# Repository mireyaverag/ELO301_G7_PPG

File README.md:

# Diseño de equipos electrónicos
## ELO301 UFTSM  
Grupo 7: Proyecto de Fotopletismografía  
* Seguimos la aplicación típica del datasheet del AFE4400
* La PCB será de color morado, pero no encontramos la forma de agregarlo en eagle como se mostró en clases

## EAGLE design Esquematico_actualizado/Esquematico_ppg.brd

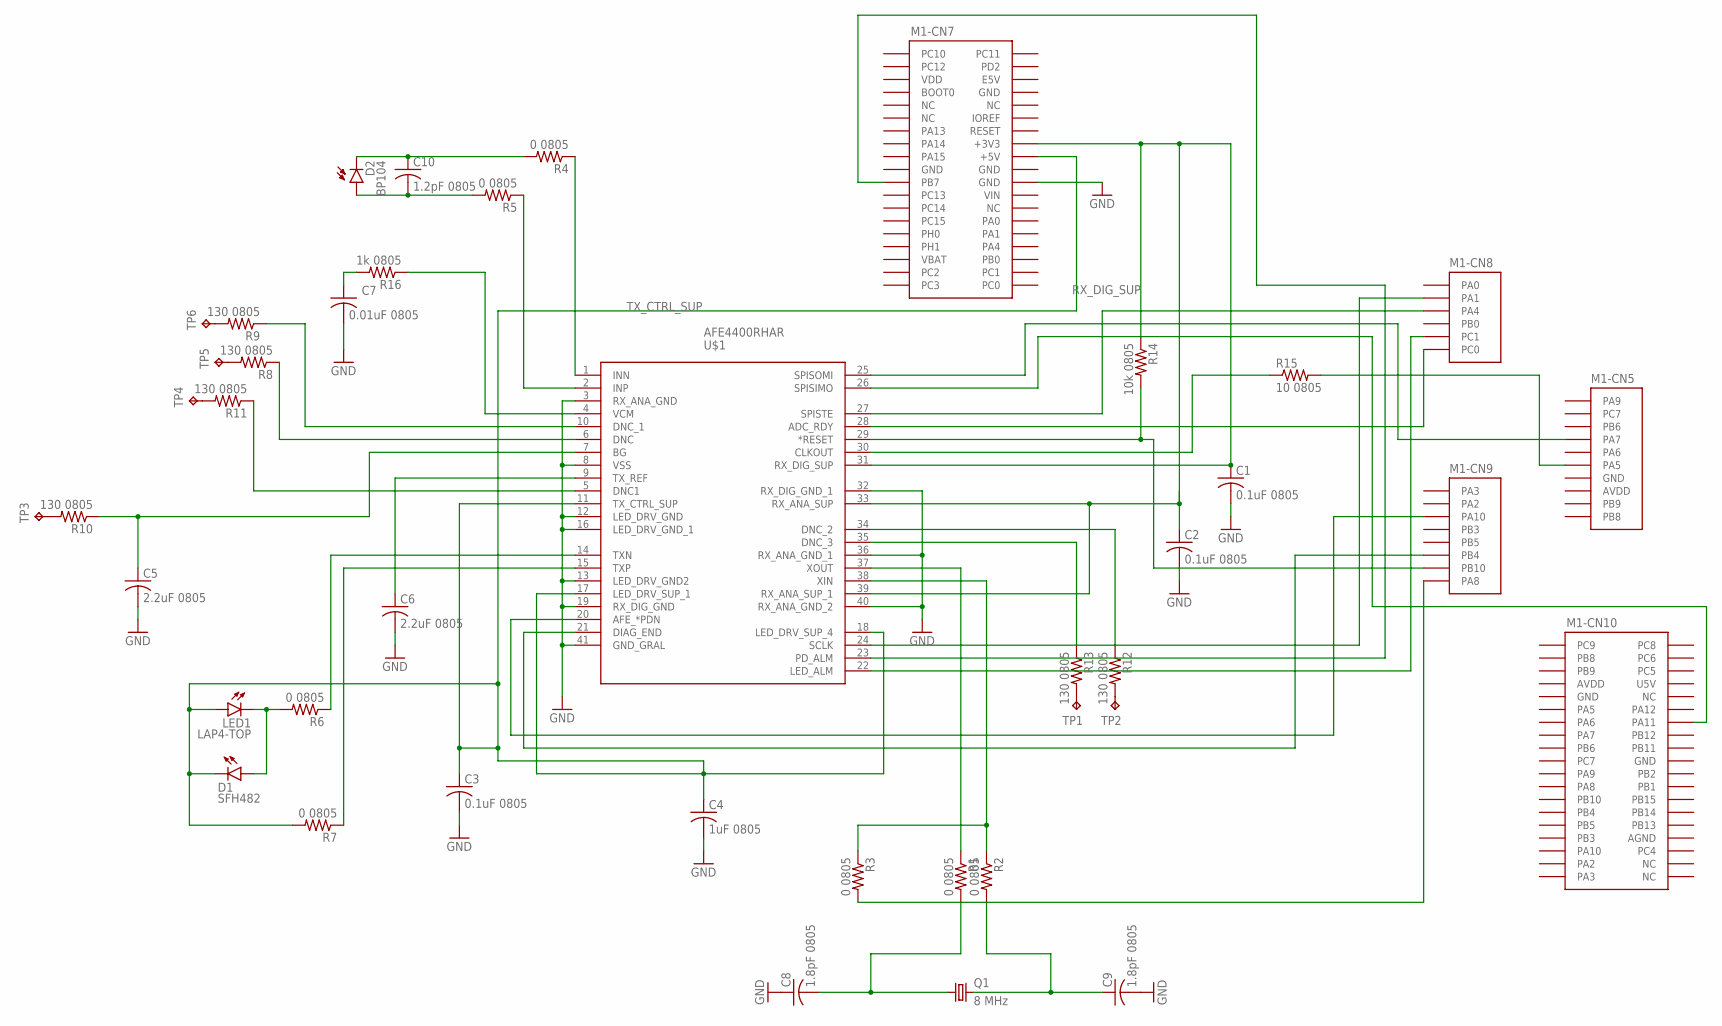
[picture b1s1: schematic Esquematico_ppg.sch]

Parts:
C1, C2, C3: 0.1uF 0805; C0805; PARTNO GRM188R72A104KA35J
C4: 1uF 0805; C0805; PARTNO GRM188R72A104KA35J
C5, C6: 2.2uF 0805; C0805; PARTNO GRM21BR71E225KE11L
C7: 0.01uF 0805; C0805; PARTNO GRM2195C1H103JA01D
C8, C9: 1.8pF 0805; C0805; PARTNO 600F180FT250XT
C10: 1.2pF 0805; C0805; PARTNO GQM2195C2E1R2BB12D
D1: SFH482; PARTNO SCM-013RT
D2: BP104; PARTNO VEMD2020X01
LED1: LAP4-TOP; P47F-TOP; PARTNO HLMP-K150
M1: NUCLEO-L452RE; NUCLEO-64
Q1: 8 MHz; SM49; PARTNO ABLS-8.000MHZ-B4-T
R1, R2, R3, R4, R5, R6, R7: 0 0805; M0805; PARTNO RMCF0805ZT0R00
R8, R9, R10, R11, R12, R13: 130 0805; M0805; PARTNO RMCF0805FT130R
R14: 10k 0805; M0805; PARTNO RC0805FR-1010KL
R15: 10 0805; M0805; PARTNO RC0805FR-0710RL
R16: 1k 0805; M0805; PARTNO RMCF0805FT1K00
TP1, TP2, TP3, TP4, TP5, TP6: TPB1,27; B1,27
U$1: AFE4400RHAR; 40-VQFN(6X6)

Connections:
+3V3: M1.CN6-4 (+3V3)
+5V: M1.CN6-5 (+5V)
AGND: M1.CN10-32 (AGND)
AVDD: M1.CN5-8 (AVDD), M1.CN10-7 (AVDD)
GND: C1.2, C2.2, C3.2, C4.2, C5.2, C6.2, C7.2, C8.1, C9.2, M1.CN5-7 (GND), M1.CN6-6 (GND), M1.CN6-7 (GND), M1.CN7-8 (GND), M1.CN7-19 (GND), M1.CN7-20 (GND), M1.CN7-22 (GND), M1.CN10-9 (GND), M1.CN10-20 (GND), U$1.3 (RX_ANA_GND), U$1.8 (VSS), U$1.12 (LED_DRV_GND), U$1.13 (LED_DRV_GND2), U$1.16 (LED_DRV_GND_1), U$1.19 (RX_DIG_GND), U$1.32 (RX_DIG_GND_1), U$1.36 (RX_ANA_GND_1), U$1.40 (RX_ANA_GND_2), U$1.41 (GND_GRAL)
IOREF: M1.CN6-2 (IOREF)
unnamed: R4.1, U$1.1 (INN)
unnamed: R5.1, U$1.2 (INP)
unnamed: R6.1, U$1.14 (TXN)
unnamed: R7.1, U$1.15 (TXP)
unnamed: R2.1, R3.1, U$1.38 (XIN)
unnamed: R1.1, U$1.37 (XOUT)
unnamed: R13.2, TP1.TP
unnamed: R12.2, TP2.TP
unnamed: R10.2, TP3.TP
unnamed: R11.1, U$1.5 (DNC1)
unnamed: R12.1, U$1.34 (DNC_2)
unnamed: R11.2, TP4.TP
unnamed: R9.1, U$1.10 (DNC_1)
unnamed: R8.1, U$1.6 (DNC)
unnamed: C5.1, R10.1, U$1.7 (BG)
unnamed: R13.1, U$1.35 (DNC_3)
unnamed: M1.CN9-7 (PB10), R14.2, U$1.29 (*RESET)
unnamed: R8.2, TP5.TP
unnamed: R15.1, U$1.30 (CLKOUT)
unnamed: M1.CN5-6 (PA5), R15.2
unnamed: M1.CN9-8 (PA8), R3.2
unnamed: M1.CN8-3 (PA4), U$1.27 (SPISTE)
unnamed: C6.1, U$1.9 (TX_REF)
unnamed: M1.CN10-14 (PA11), U$1.26 (SPISIMO)
unnamed: R16.1, U$1.4 (VCM)
unnamed: C7.1, R16.2
unnamed: C8.2, Q1.1, R1.2
unnamed: C9.1, Q1.2, R2.2
unnamed: M1.CN5-4 (PA7), U$1.25 (SPISOMI)
unnamed: M1.CN7-21 (PB7), U$1.23 (PD_ALM)
unnamed: M1.CN8-5 (PC1), U$1.22 (LED_ALM)
unnamed: M1.CN8-6 (PC0), U$1.28 (ADC_RDY)
unnamed: M1.CN9-3 (PA10), U$1.20 (AFE_*PDN)
unnamed: M1.CN9-6 (PB4), U$1.21 (DIAG_END)
unnamed: D1.A, LED1.C, R6.2
unnamed: R9.2, TP6.TP
unnamed: C10.2, D2.A, R5.2
unnamed: C10.1, D2.K (C), R4.2
RX_DIG_SUP: C1.1, C2.1, M1.CN7-16 (+3V3), R14.1, U$1.31 (RX_DIG_SUP), U$1.33 (RX_ANA_SUP), U$1.39 (RX_ANA_SUP_1)
SCLK: M1.CN8-2 (PA1), U$1.24 (SCLK)
TX_CTRL_SUP: C3.1, C4.1, D1.K (C), LED1.A, M1.CN7-18 (+5V), R7.2, U$1.11 (TX_CTRL_SUP), U$1.17 (LED_DRV_SUP_1), U$1.18 (LED_DRV_SUP_4)
U5V: M1.CN10-8 (U5V)
VBAT: M1.CN7-33 (VBAT)
VDD: M1.CN7-5 (VDD)
VIN: M1.CN6-8 (VIN), M1.CN7-24 (VIN)

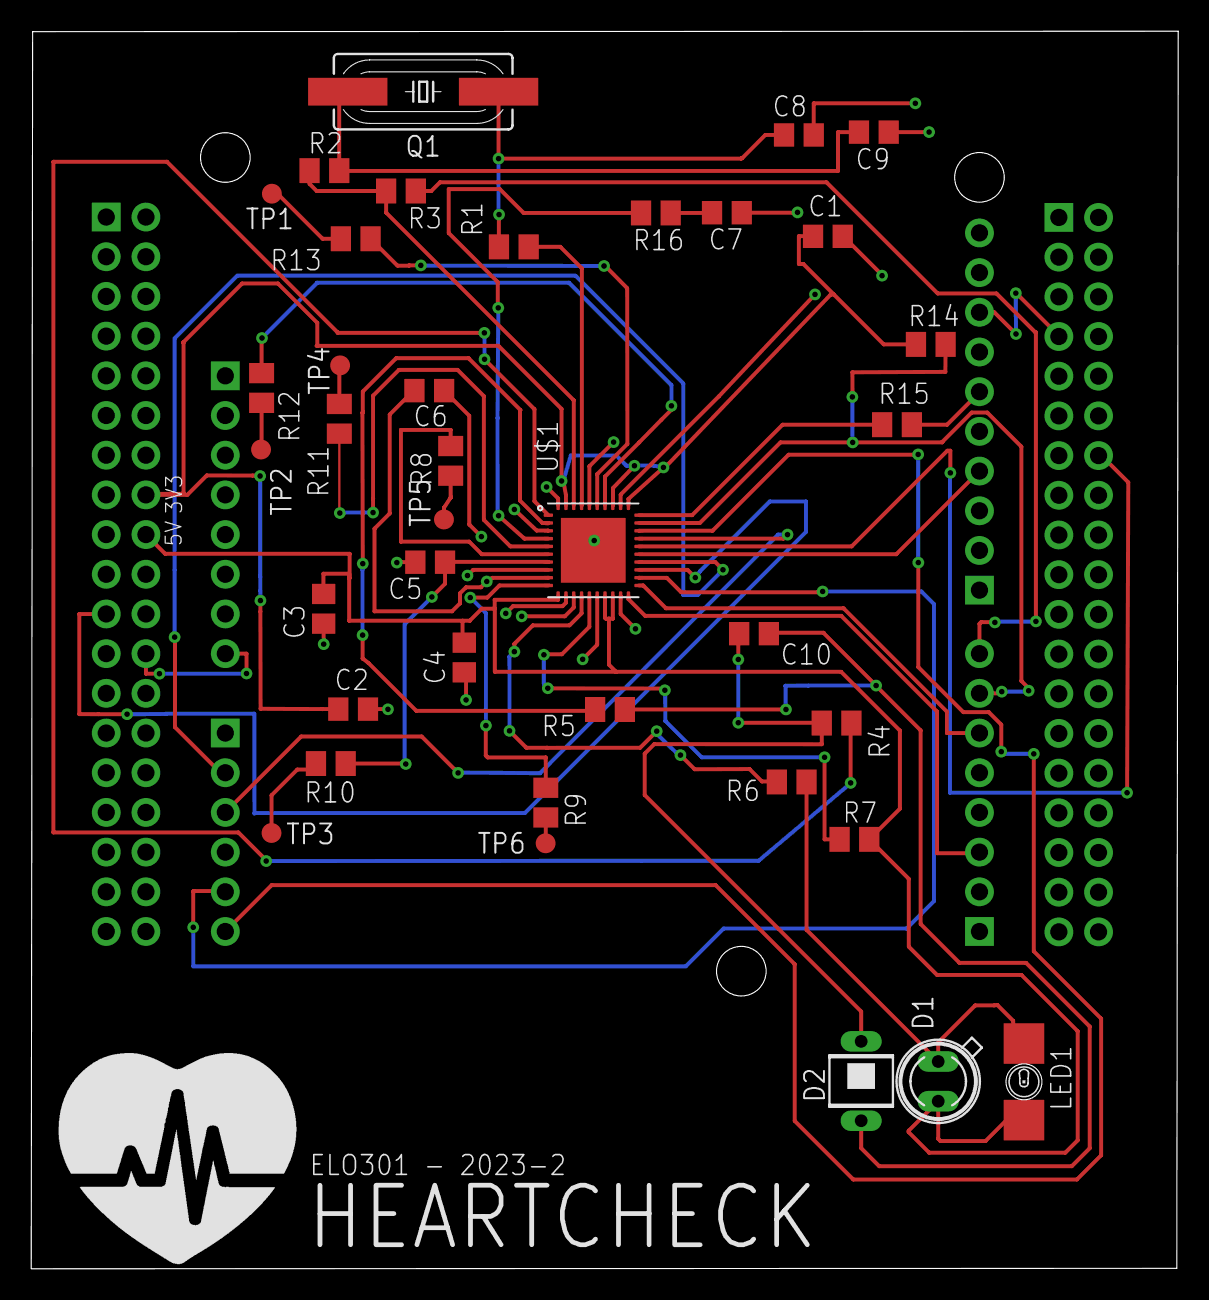
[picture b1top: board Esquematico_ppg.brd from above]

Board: 2 copper layers, 73.4 x 79.2 mm, 38 parts (0 on the bottom side), 44 nets.

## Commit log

2023-10-31 Rename Diseño_PCB/.algo to Diseño_PCB/Assembly/.algo
2023-10-31 DrillFiles
2023-10-31 GerberFiles
2023-10-31 Esquematico
